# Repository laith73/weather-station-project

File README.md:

# Project Description

This is a design for a weather station device that provides multiple essential metrics for real-world weather scenarios. This device can be used in various settings, including homes, farms, and offices, allowing users to gain insight into the weather without leaving the comfort of their own place. Additionally, the device provides a simple web dashboard accessible locally to display the sensors' readings on the user's computer or phone, as well as a small OLED display on the device for easy local monitoring.

This repo contains all of the KiCad project files, reports, and datasheets for the parts used.

# Contributors

- Laith Al Sairafi, laith73@iastate.edu
- Luke Post, lpost@iastate.edu

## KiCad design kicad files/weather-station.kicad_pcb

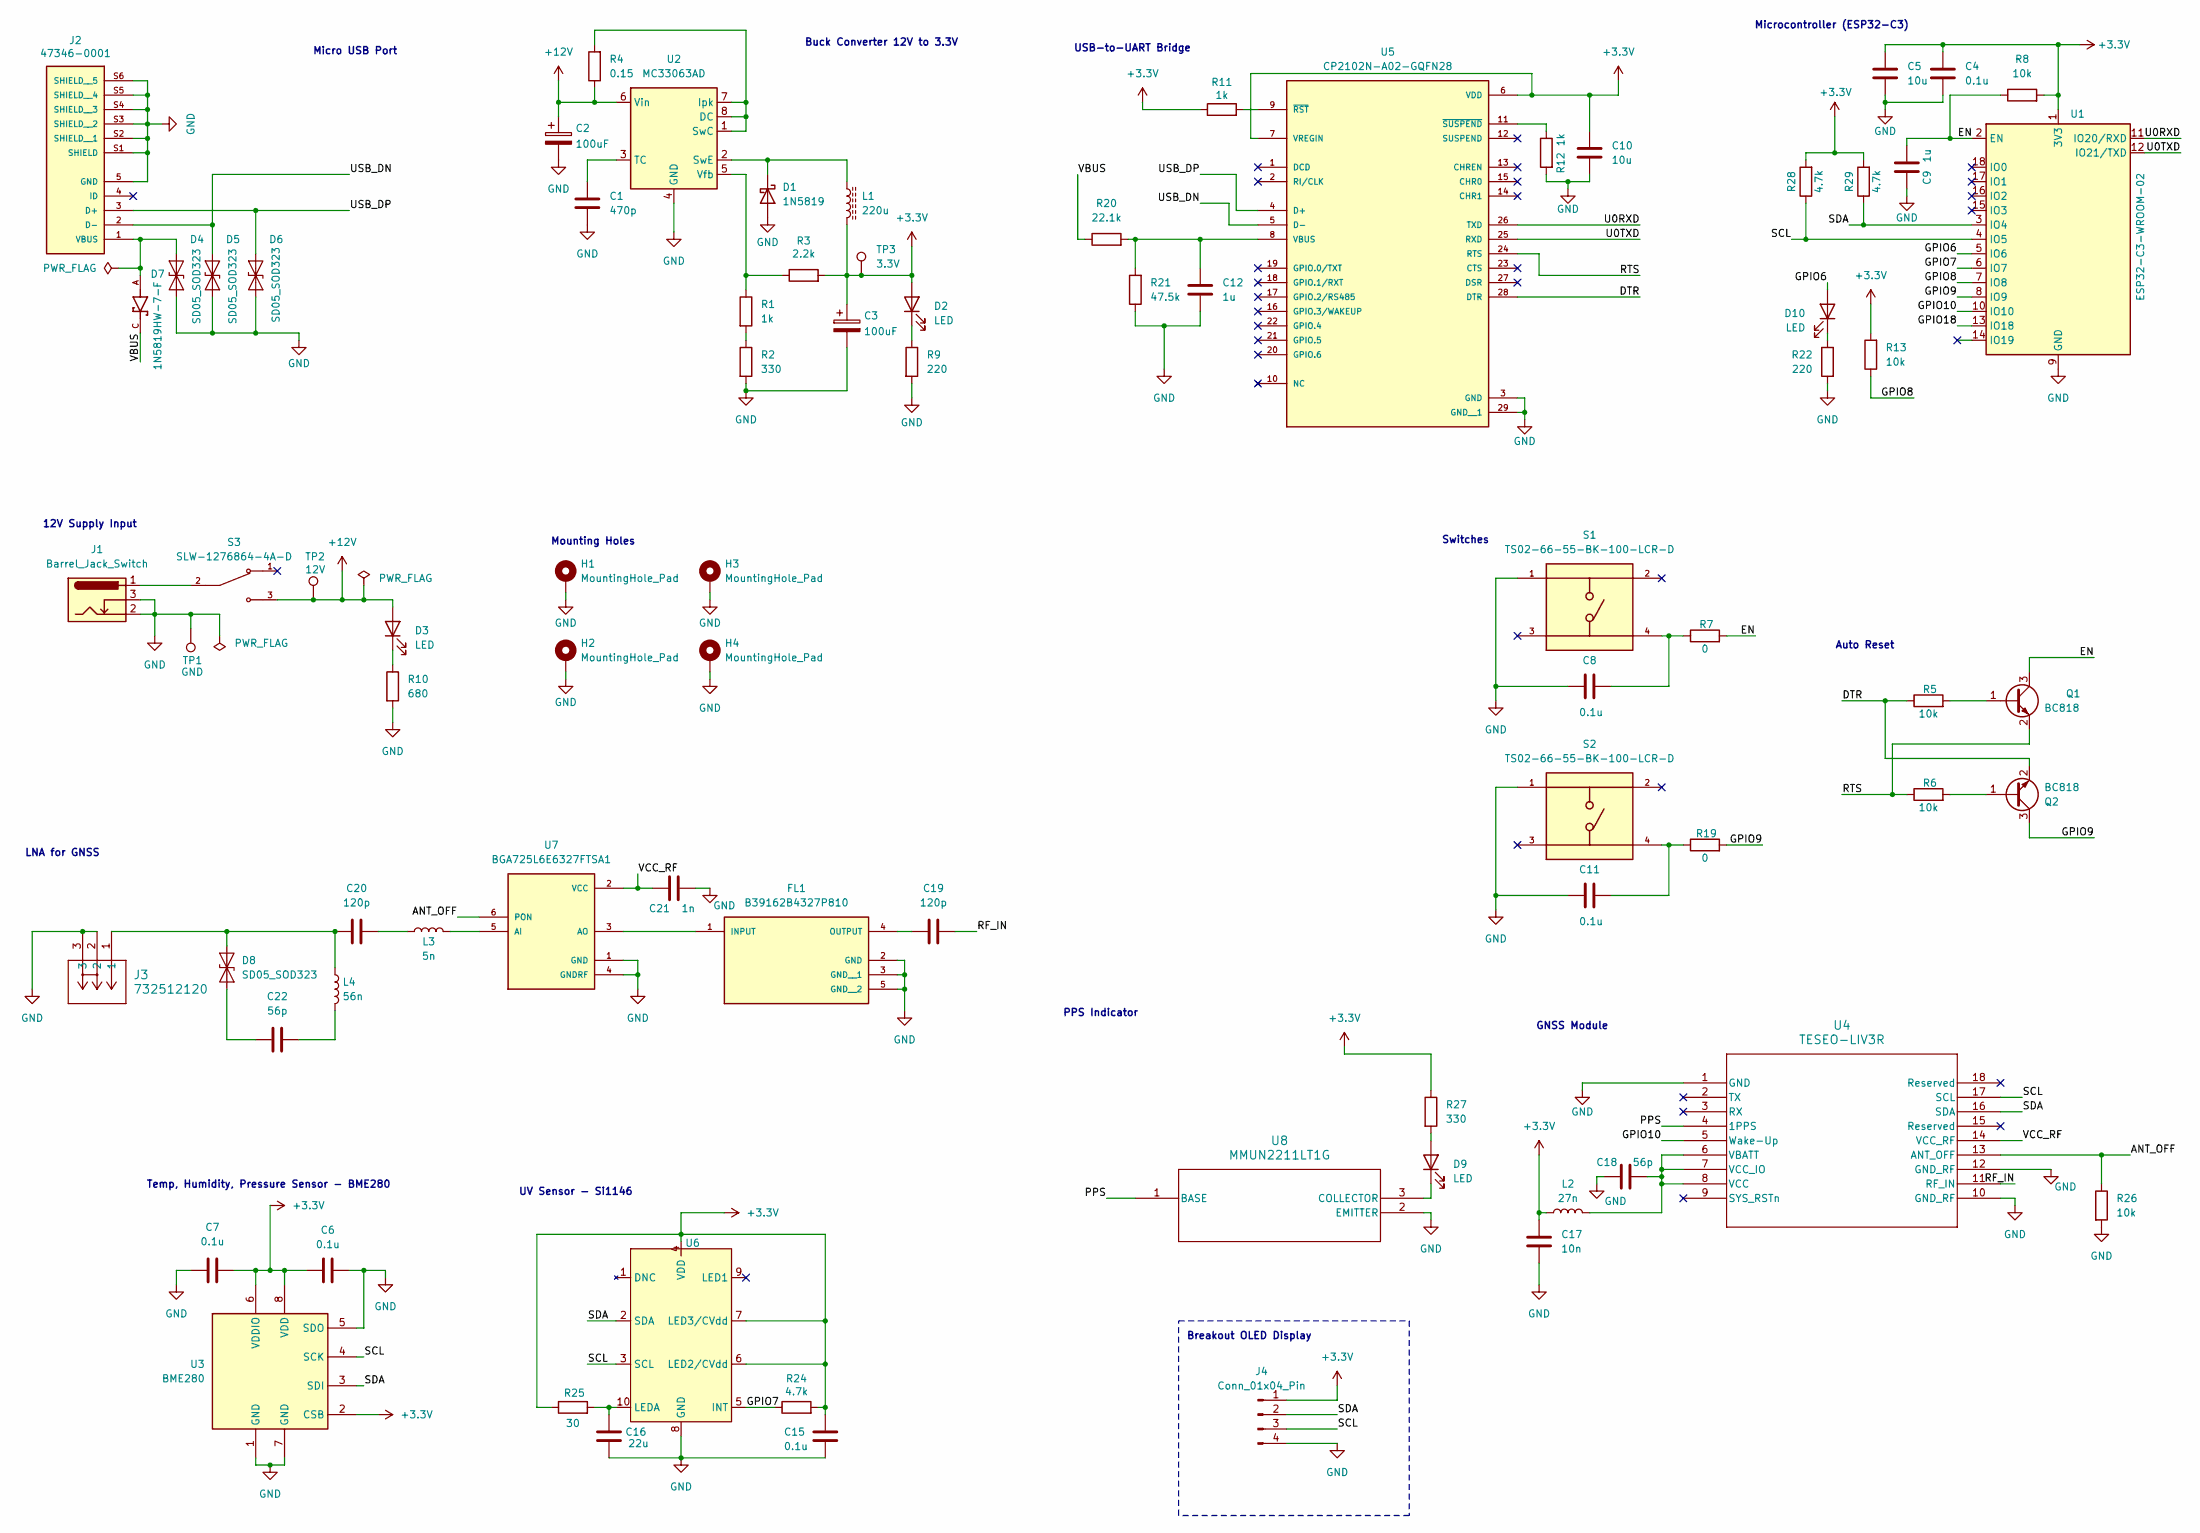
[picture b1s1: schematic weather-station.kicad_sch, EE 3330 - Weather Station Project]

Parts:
C1: 470p; C_0805_2012Metric_Pad1.18x1.45mm_HandSolder
C2, C3: 100uF; CP_Radial_D10.0mm_P5.00mm
C4, C6, C7, C8, C11, C15: 0.1u; C_0805_2012Metric_Pad1.18x1.45mm_HandSolder
C5, C10: 10u; C_0805_2012Metric_Pad1.18x1.45mm_HandSolder
C9, C12: 1u; C_0805_2012Metric_Pad1.18x1.45mm_HandSolder
C16: 22u; C_0805_2012Metric_Pad1.18x1.45mm_HandSolder
C17: 10n; C_0402_1005Metric_Pad0.74x0.62mm_HandSolder
C18, C22: 56p; C_0402_1005Metric_Pad0.74x0.62mm_HandSolder
C19, C20: 120p; C_0402_1005Metric_Pad0.74x0.62mm_HandSolder
C21: 1n; C_0402_1005Metric_Pad0.74x0.62mm_HandSolder
D1: 1N5819; D_DO-41_SOD81_P10.16mm_Horizontal
D2, D3, D9, D10: LED; LED_1206_3216Metric_Pad1.42x1.75mm_HandSolder
D4, D5, D6, D8: SD05_SOD323; D_SOD-323
D7: 1N5819HW-7-F; SOD3715X145N; PARTREV 18-2
FL1: B39162B4327P810; FIL_B39162B4327P810; PARTREV October 25, 2019
H1, H2, H3, H4: MountingHole_Pad; MountingHole_3.2mm_M3_ISO7380_Pad_TopBottom
J1: Barrel_Jack_Switch; BarrelJack_Horizontal
J2: 47346-0001; MOLEX_47346-0001; PARTREV E
J3: 732512120; CONN-732513152_MOL
J4: Conn_01x04_Pin; PinSocket_1x04_P2.54mm_Vertical
L1: 220u; IND_RLB9012-221KL
L2: 27n; L_0402_1005Metric_Pad0.77x0.64mm_HandSolder
L3: 5n; L_0402_1005Metric_Pad0.77x0.64mm_HandSolder
L4: 56n; L_0402_1005Metric_Pad0.77x0.64mm_HandSolder
Q1, Q2: BC818; SOT-23
R1, R11, R12: 1k; R_0805_2012Metric_Pad1.20x1.40mm_HandSolder
R2, R27: 330; R_0805_2012Metric_Pad1.20x1.40mm_HandSolder
R3: 2.2k; R_0805_2012Metric_Pad1.20x1.40mm_HandSolder
R4: 0.15; R_0805_2012Metric_Pad1.20x1.40mm_HandSolder
R5, R6, R8, R13: 10k; R_0805_2012Metric_Pad1.20x1.40mm_HandSolder
R7, R19: 0; R_0805_2012Metric_Pad1.20x1.40mm_HandSolder
R9, R22: 220; R_0805_2012Metric_Pad1.20x1.40mm_HandSolder
R10: 680; R_0805_2012Metric_Pad1.20x1.40mm_HandSolder
R20: 22.1k; R_0805_2012Metric_Pad1.20x1.40mm_HandSolder
R21: 47.5k; R_0805_2012Metric_Pad1.20x1.40mm_HandSolder
R24, R28, R29: 4.7k; R_0805_2012Metric_Pad1.20x1.40mm_HandSolder
R25: 30; R_0805_2012Metric_Pad1.20x1.40mm_HandSolder
R26: 10k; R_0402_1005Metric_Pad0.72x0.64mm_HandSolder
S1, S2: TS02-66-55-BK-100-LCR-D; SW_TS02-66-55-BK-100-LCR-D; PARTREV 1.0
S3: SLW-1276864-4A-D; SW_SLW-1276864-4A-D; PARTREV 1.01
TP1: GND; TestPoint_Keystone_5010-5014_Multipurpose
TP2: 12V; TestPoint_Keystone_5010-5014_Multipurpose
TP3: 3.3V; TestPoint_Keystone_5010-5014_Multipurpose
U1: ESP32-C3-WROOM-02
U2: MC33063AD; SOIC-8_3.9x4.9mm_P1.27mm
U3: BME280; Bosch_LGA-8_2.5x2.5mm_P0.65mm_ClockwisePinNumbering
U4: TESEO-LIV3R; ARRAY_LIV3R_STM
U5: CP2102N-A02-GQFN28; QFN50P500X500X80-29N; PARTREV 1.5
U6: Si1146; QFN-10_2.85x4.9_Pitch1mm
U7: BGA725L6E6327FTSA1; AMP_BGA725L6E6327FTSA1; PARTREV 2.0
U8: MMUN2211LT1G; SOT-23-3_1P4X3P040_ONS

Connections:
+3.3V: C3.1, C4.1, C5.1, C6.2, C7.1, C10.1, C15.1, C17.1, D2.2 (A), J4.1, L1.2, L2.1, R3.2, R8.2, R11.1, R13.2, R24.2, R25.1, R27.1, R28.2, R29.2, TP3.1, U1.1 (3V3), U3.2 (CSB), U3.6 (VDDIO), U3.8 (VDD), U5.6 (VDD), U5.7 (VREGIN), U6.4 (VDD), U6.6 (LED2/CVdd), U6.7 (LED3/CVdd)
+12V: C2.1, D3.2 (A), R4.1, S3.3, TP2.1, U2.6 (Vin)
/ANT_OFF: R26.1, U4.13 (ANT_OFF), U7.6 (PON)
/DTR: Q2.2 (E), R5.1, U5.28 (DTR)
/EN: C9.2, Q1.3 (C), R7.2, R8.1, U1.2 (EN)
/GPIO6: D10.2 (A), U1.5 (IO6)
/GPIO7: R24.1, U1.6 (IO7), U6.5 (INT)
/GPIO8: R13.1, U1.7 (IO8)
/GPIO9: Q2.3 (C), R19.2, U1.8 (IO9)
/GPIO10: U1.10 (IO10), U4.5 (Wake-Up)
/GPIO18: U1.13 (IO18)
/PPS: U4.4 (1PPS), U8.1 (BASE)
/RF_IN: C19.2, U4.11 (RF_IN)
/RTS: Q1.2 (E), R6.1, U5.24 (RTS)
/SCL: J4.3, R28.1, U1.4 (IO5), U3.4 (SCK), U4.17 (SCL), U6.3 (SCL)
/SDA: J4.2, R29.1, U1.3 (IO4), U3.3 (SDI), U4.16 (SDA), U6.2 (SDA)
/U0RXD: U1.11 (IO20/RXD), U5.26 (TXD)
/U0TXD: U1.12 (IO21/TXD), U5.25 (RXD)
/USB_DN: D5.2 (A2), J2.2 (D-), U5.5 (D-)
/USB_DP: D6.2 (A2), J2.3 (D+), U5.4 (D+)
/VBUS: D7.C, R20.1
/VCC_RF: C21.1, U4.14 (VCC_RF), U7.2 (VCC)
GND: C1.2, C2.2, C3.2, C4.2, C5.2, C6.1, C7.2, C8.1, C9.1, C10.2, C11.1, C12.2, C15.2, C16.2, C17.2, C18.1, C21.2, D1.2 (A), D4.1 (A1), D5.1 (A1), D6.1 (A1), FL1.2 (GND), FL1.3 (GND__1), FL1.5 (GND__2), H1.1, H2.1, H3.1, H4.1, J1.2, J1.3, J2.5 (GND), J2.S1 (SHIELD), J2.S2 (SHIELD__1), J2.S3 (SHIELD__2), J2.S4 (SHIELD__3), J2.S5 (SHIELD__4), J2.S6 (SHIELD__5), J3.2, J3.3, J4.4, R2.2, R9.2, R10.2, R12.2, R21.1, R22.2, R26.2, S1.1, S2.1, TP1.1, U1.9 (GND), U1.19 (GND), U2.4 (GND), U3.1 (GND), U3.5 (SDO), U3.7 (GND), U4.1 (GND), U4.10 (GND_RF), U4.12 (GND_RF), U5.3 (GND), U5.29 (GND__1), U6.8 (GND), U7.1 (GND), U7.4 (GNDRF), U8.2 (EMITTER)
unnamed: C8.2, R7.1, S1.4
unnamed: C11.2, R19.1, S2.4
unnamed: C20.2, L3.1
unnamed: C22.2, L4.2
unnamed: D1.1 (K), L1.1, U2.2 (SwE)
unnamed: D2.1 (K), R9.1
unnamed: D3.1 (K), R10.1
unnamed: D4.2 (A2), D7.A, J2.1 (VBUS)
unnamed: C22.1, D8.1 (A1)
unnamed: C20.1, D8.2 (A2), J3.1, L4.1
unnamed: D9.2 (A), R27.2
unnamed: D9.1 (K), U8.3 (COLLECTOR)
unnamed: D10.1 (K), R22.1
unnamed: FL1.1 (INPUT), U7.3 (AO)
unnamed: C19.1, FL1.4 (OUTPUT)
unnamed: J1.1, S3.2
unnamed: Q1.1 (B), R5.2
unnamed: Q2.1 (B), R6.2
unnamed: R1.2, R2.1
unnamed: R4.2, U2.1 (SwC), U2.7 (Ipk), U2.8 (DC)
unnamed: C1.1, U2.3 (TC)
unnamed: R1.1, R3.1, U2.5 (Vfb)
unnamed: C18.2, L2.2, U4.6 (VBATT), U4.7 (VCC_IO), U4.8 (VCC)
unnamed: C12.1, R20.2, R21.2, U5.8 (VBUS)
unnamed: R11.2, U5.9 (~RST)
unnamed: R12.1, U5.11 (~SUSPEND)
unnamed: C16.1, R25.2, U6.10 (LEDA)
unnamed: L3.2, U7.5 (AI)

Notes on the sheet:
Auto Reset
12V Supply Input
Switches
USB-to-UART Bridge
UV Sensor - Si1146
LNA for GNSS
GNSS Module
Temp, Humidity, Pressure Sensor - BME280
PPS Indicator
Breakout OLED Display
Microcontroller (ESP32-C3)
Buck Converter 12V to 3.3V
Micro USB Port
Mounting Holes

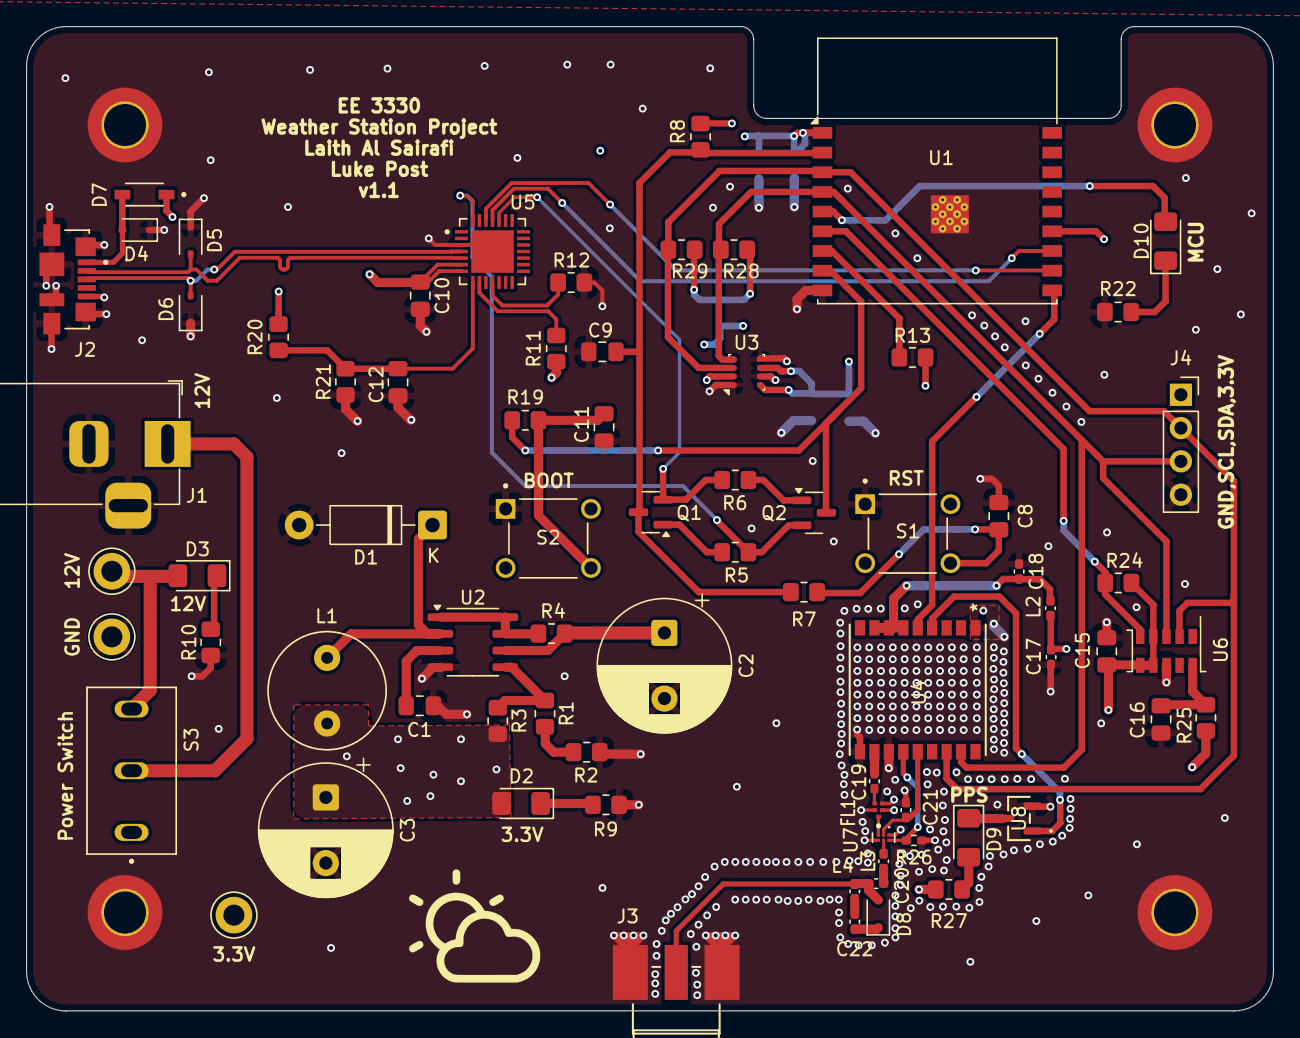
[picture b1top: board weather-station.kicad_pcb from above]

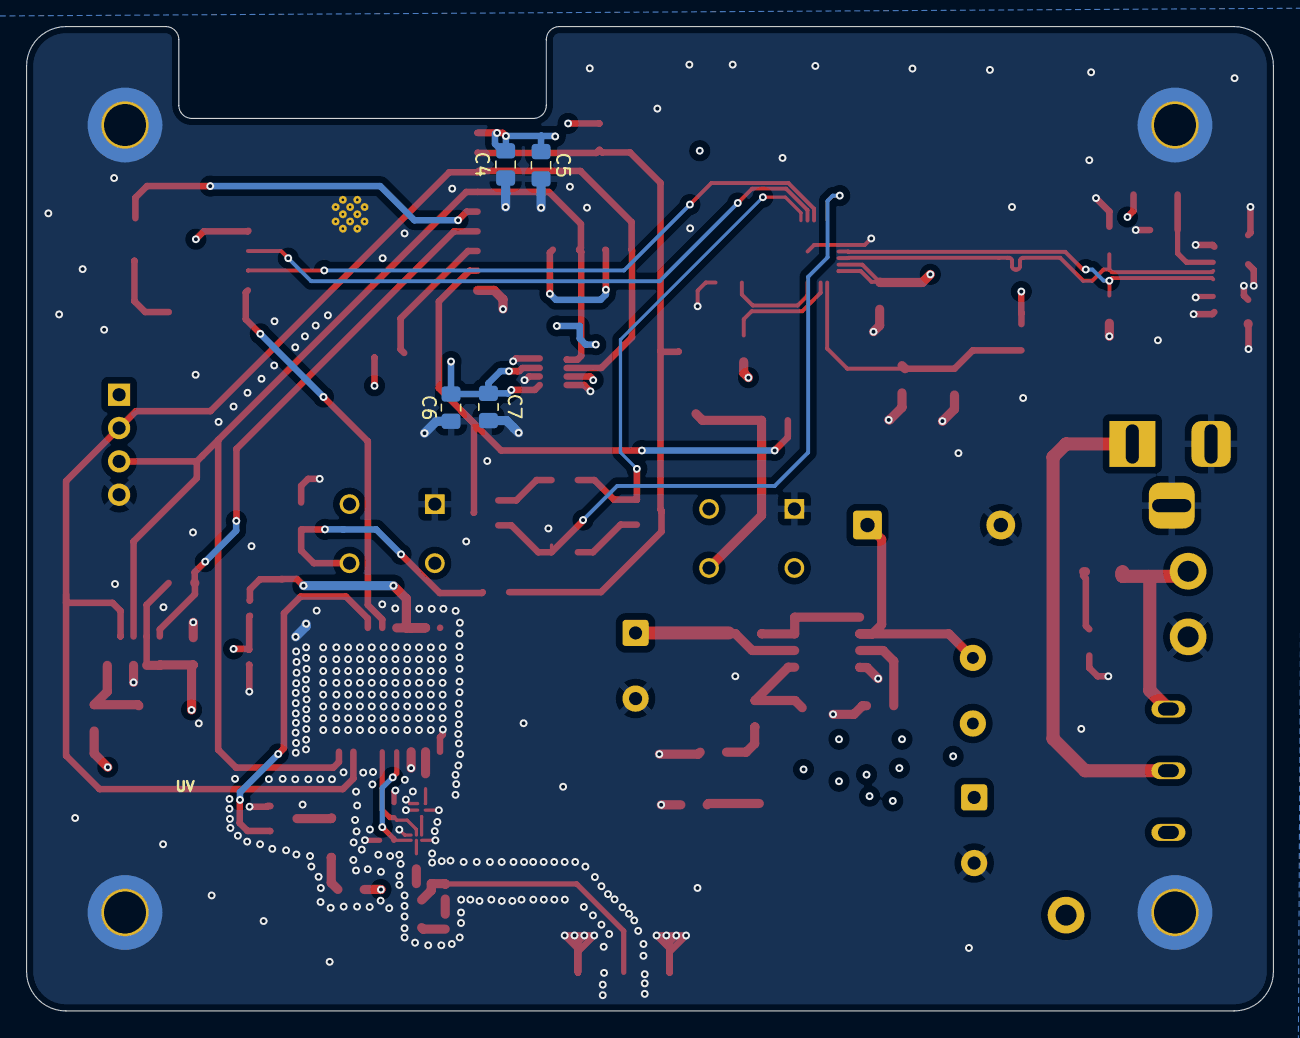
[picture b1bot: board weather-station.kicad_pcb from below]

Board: 4 copper layers, 95.0 x 75.0 mm, 82 parts (4 on the bottom side), 50 nets.

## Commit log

2026-01-02 gitignore updated.
2026-02-09 edit README.md
